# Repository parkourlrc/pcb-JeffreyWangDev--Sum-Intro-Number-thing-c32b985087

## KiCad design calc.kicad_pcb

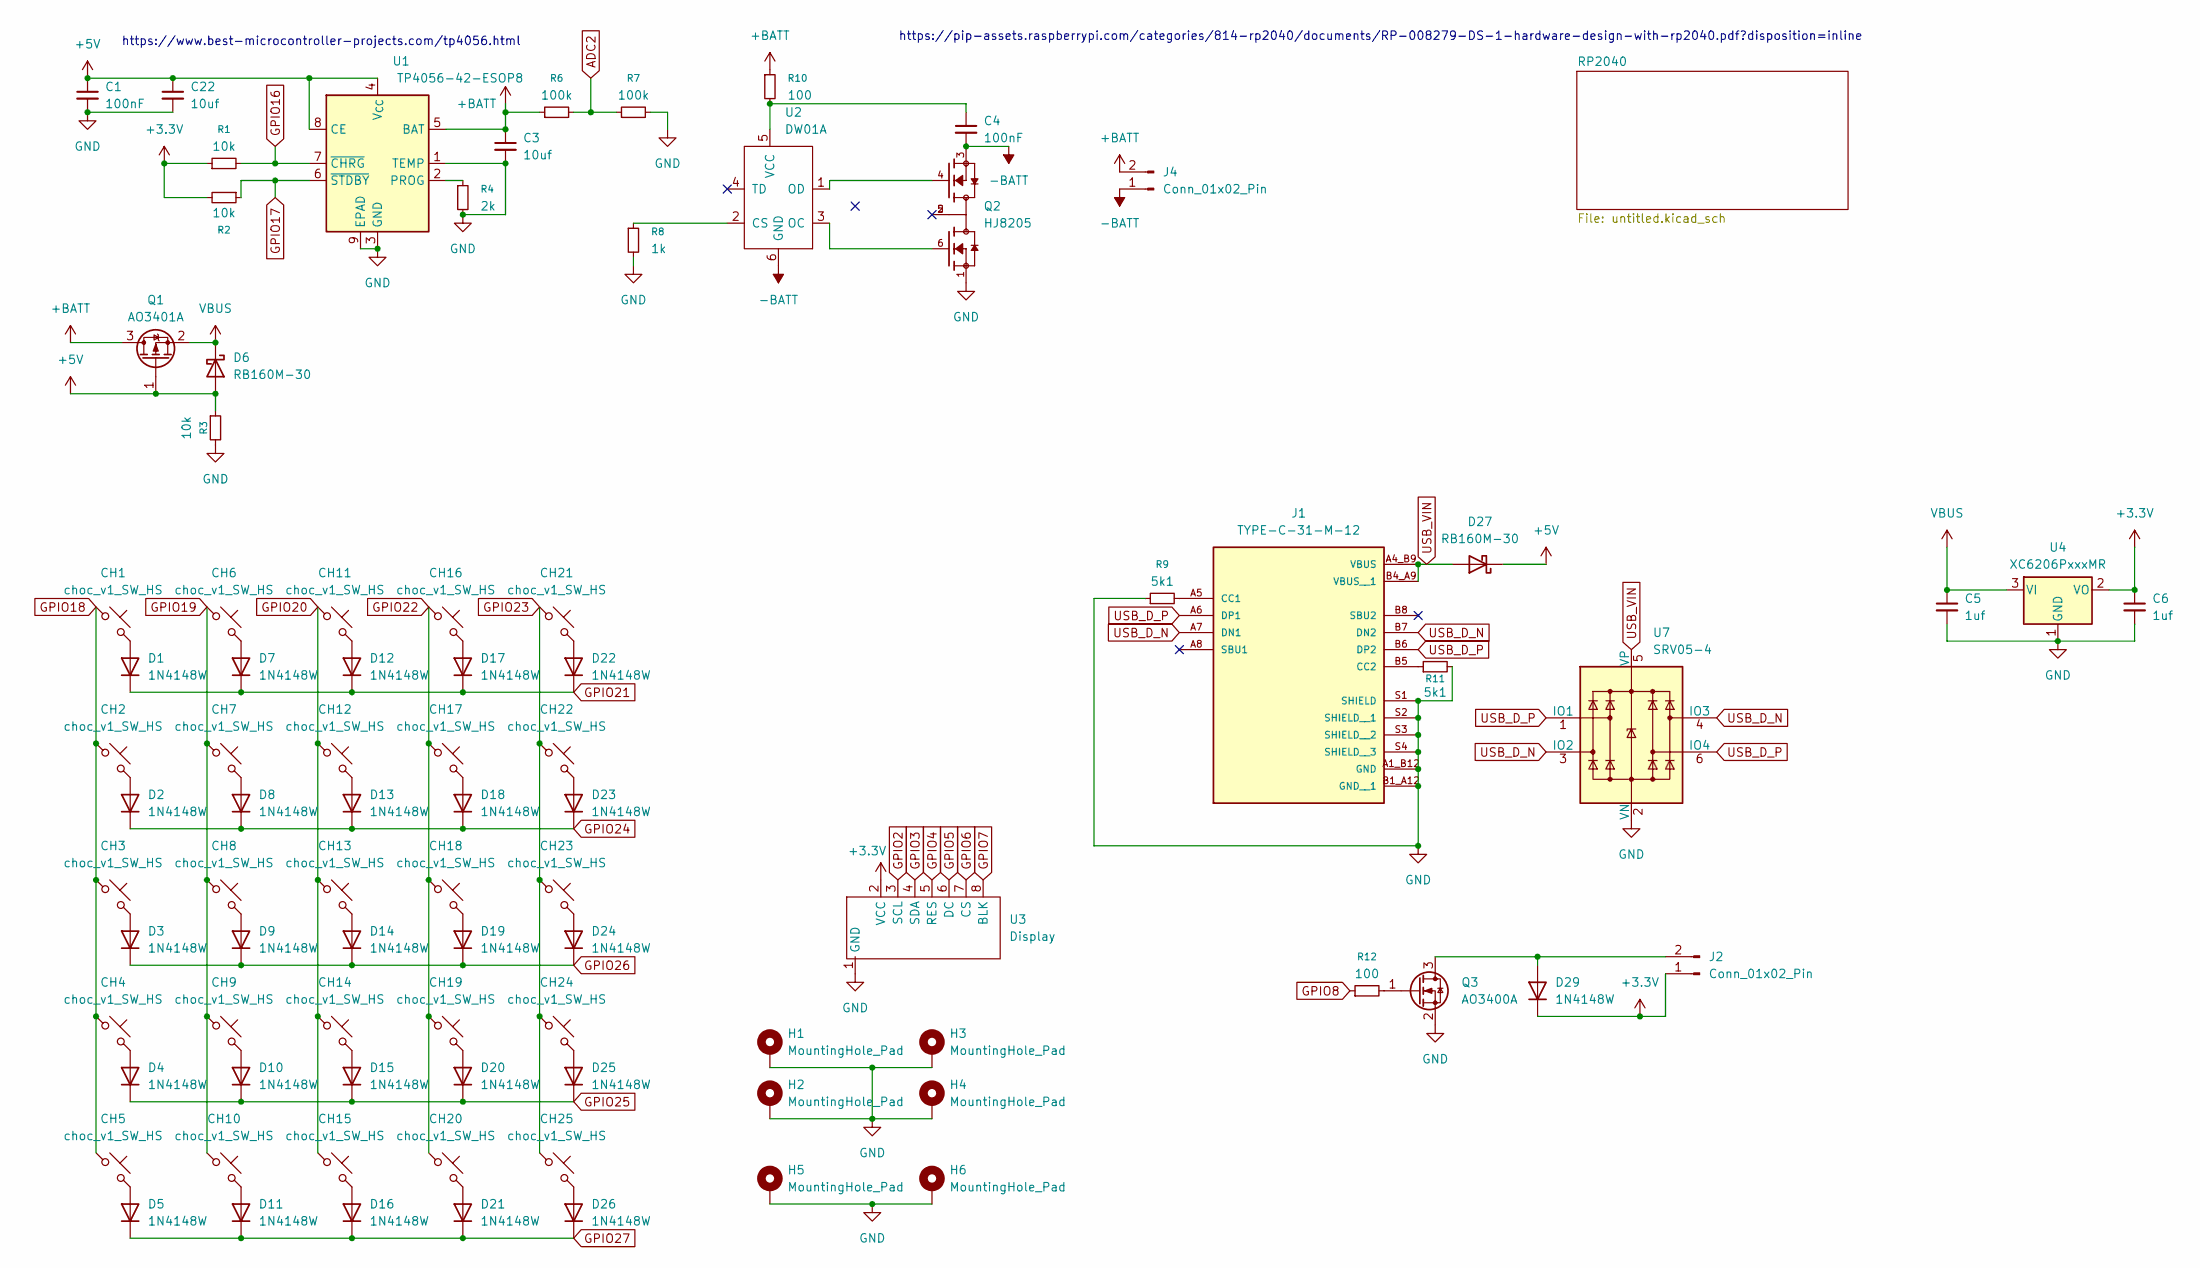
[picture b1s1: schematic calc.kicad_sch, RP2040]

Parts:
C1, C4: 100nF; C_0402_1005Metric; lcsc C1525
C3, C22: 10uf; C_0603_1608Metric; lcsc C96446
C5, C6: 1uf; C_0805_2012Metric_Pad1.18x1.45mm_HandSolder; lcsc C28323
CH1, CH2, CH3, CH4, CH5, CH6, CH7, CH8, CH9, CH10, CH11, CH12, CH13, CH14, CH15, CH16, CH17, CH18, CH19, CH20, CH21, CH22, CH23, CH24, CH25: choc_v1_SW_HS; SW_choc_v1_HS_CPG135001S30_1u
D1, D2, D3, D4, D5, D7, D8, D9, D10, D11, D12, D13, D14, D15, D16, D17, D18, D19, D20, D21, D22, D23, D24, D25, D26, D29: 1N4148W; D_SOD-123; lcsc C81598
D6, D27: RB160M-30; D_SOD-123; LCSC C7502715
H1, H2, H3, H4, H5, H6: MountingHole_Pad; MountingHole_3.2mm_M3_ISO14580_Pad_TopBottom
J1: TYPE-C-31-M-12; HRO_TYPE-C-31-M-12; PARTREV 2020.12.08; LCSC C165948
J2, J4: Conn_01x02_Pin; PinHeader_1x02_P2.00mm_Vertical
Q1: AO3401A; SOT-23; LCSC C15127
Q2: HJ8205; SOT-23-6; LCSC C20069150
Q3: AO3400A; SOT-23; lcsc C20917
R1, R2, R3: 10k; R_0805_2012Metric_Pad1.20x1.40mm_HandSolder; lcsc C17414
R4: 2k; R_0402_1005Metric; lcsc C4109
R6, R7: 100k; R_0603_1608Metric; lcsc C25803
R8: 1k; R_0402_1005Metric; lcsc C11702
R9, R11: 5k1; R_0402_1005Metric; lcsc C25905
R10, R12: 100; R_0805_2012Metric_Pad1.20x1.40mm_HandSolder; lcsc C17408
U1: TP4056-42-ESOP8; SOIC-8-1EP_3.9x4.9mm_P1.27mm_EP2.41x3.3mm_ThermalVias; LCSC C16581
U2: DW01A; SOT-23-6; LCSC C351410
U3: Display; 2.25_ TFT
U4: XC6206PxxxMR; SOT-23-3; LCSC C5446
U7: SRV05-4; SOT-23-6; lcsc C85364

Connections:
+3.3V: C6.1, D29.1 (K), J2.1, R1.1, R2.2, U3.2 (VCC), U4.2 (VO); also elsewhere on the board
+5V: C1.1, C22.1, D6.2 (A), D27.1 (K), Q1.1 (G), R3.1, U1.4 (V_{CC}), U1.8 (CE)
+BATT: C3.1, J4.2, Q1.3 (D), R6.1, R10.1, U1.5 (BAT)
-BATT: C4.2, J4.1, Q2.3, U2.6 (GND)
ADC2: R6.2, R7.1; also elsewhere on the board
GND: C1.2, C3.2, C5.2, C6.2, C22.2, H1.1 (1_1), H2.1 (1_1), H3.1 (1_1), H4.1 (1_1), H5.1 (1_1), H6.1 (1_1), J1.A1_B12 (GND), J1.B1_A12 (GND__1), J1.S1 (SHIELD), J1.S2 (SHIELD__1), J1.S3 (SHIELD__2), J1.S4 (SHIELD__3), Q2.1, Q3.2 (S), R3.2, R4.2, R7.2, R8.2, R9.1, R11.2, U1.1 (TEMP), U1.3 (GND), U1.9 (EPAD), U3.1 (GND), U4.1 (GND), U7.2 (VN); also elsewhere on the board
GPIO2: U3.3 (SCL); also elsewhere on the board
GPIO3: U3.4 (SDA); also elsewhere on the board
GPIO4: U3.5 (RES); also elsewhere on the board
GPIO5: U3.6 (DC); also elsewhere on the board
GPIO6: U3.7 (CS); also elsewhere on the board
GPIO7: U3.8 (BLK); also elsewhere on the board
GPIO8: R12.1; also elsewhere on the board
GPIO16: R1.2, U1.7 (~CHRG); also elsewhere on the board
GPIO17: R2.1, U1.6 (~STDBY); also elsewhere on the board
GPIO18: CH1.1, CH2.1, CH3.1, CH4.1, CH5.1; also elsewhere on the board
GPIO19: CH6.1, CH7.1, CH8.1, CH9.1, CH10.1; also elsewhere on the board
GPIO20: CH11.1, CH12.1, CH13.1, CH14.1, CH15.1; also elsewhere on the board
GPIO21: D1.1 (K), D7.1 (K), D12.1 (K), D17.1 (K), D22.1 (K); also elsewhere on the board
GPIO22: CH16.1, CH17.1, CH18.1, CH19.1, CH20.1; also elsewhere on the board
GPIO23: CH21.1, CH22.1, CH23.1, CH24.1, CH25.1; also elsewhere on the board
GPIO24: D2.1 (K), D8.1 (K), D13.1 (K), D18.1 (K), D23.1 (K); also elsewhere on the board
GPIO25: D4.1 (K), D10.1 (K), D15.1 (K), D20.1 (K), D25.1 (K); also elsewhere on the board
GPIO26: D3.1 (K), D9.1 (K), D14.1 (K), D19.1 (K), D24.1 (K); also elsewhere on the board
GPIO27: D5.1 (K), D11.1 (K), D16.1 (K), D21.1 (K), D26.1 (K); also elsewhere on the board
unnamed: CH1.2, D1.2 (A)
unnamed: CH2.2, D2.2 (A)
unnamed: CH3.2, D3.2 (A)
unnamed: CH4.2, D4.2 (A)
unnamed: CH5.2, D5.2 (A)
unnamed: CH6.2, D7.2 (A)
unnamed: CH7.2, D8.2 (A)
unnamed: CH8.2, D9.2 (A)
unnamed: CH9.2, D10.2 (A)
unnamed: CH10.2, D11.2 (A)
unnamed: CH11.2, D12.2 (A)
unnamed: CH12.2, D13.2 (A)
unnamed: CH13.2, D14.2 (A)
unnamed: CH14.2, D15.2 (A)
unnamed: CH15.2, D16.2 (A)
unnamed: CH16.2, D17.2 (A)
unnamed: CH17.2, D18.2 (A)
unnamed: CH18.2, D19.2 (A)
unnamed: CH19.2, D20.2 (A)
unnamed: CH20.2, D21.2 (A)
unnamed: CH21.2, D22.2 (A)
unnamed: CH22.2, D23.2 (A)
unnamed: CH23.2, D24.2 (A)
unnamed: CH24.2, D25.2 (A)
unnamed: CH25.2, D26.2 (A)
unnamed: D29.2 (A), J2.2, Q3.3 (D)
unnamed: J1.A5 (CC1), R9.2
unnamed: J1.B5 (CC2), R11.1
unnamed: Q3.1 (G), R12.2
unnamed: R4.1, U1.2 (PROG)
unnamed: R8.1, U2.2 (CS)
unnamed: Q2.6, U2.3 (OC)
unnamed: Q2.4, U2.1 (OD)
unnamed: C4.1, R10.2, U2.5 (VCC)
USB_D_N: J1.A7 (DN1), J1.B7 (DN2), U7.3 (IO2), U7.4 (IO3); also elsewhere on the board
USB_D_P: J1.A6 (DP1), J1.B6 (DP2), U7.1 (IO1), U7.6 (IO4); also elsewhere on the board
USB_VIN: D27.2 (A), J1.A4_B9 (VBUS), J1.B4_A9 (VBUS__1), U7.5 (VP)
VBUS: C5.1, D6.1 (K), Q1.2 (S), U4.3 (VI)

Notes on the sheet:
https://www.best-microcontroller-projects.com/tp4056.html
https://pip-assets.raspberrypi.com/categories/814-rp2040/documents/RP-008279-DS-1-hardware-design-with-rp2040.pdf?disposition=inline

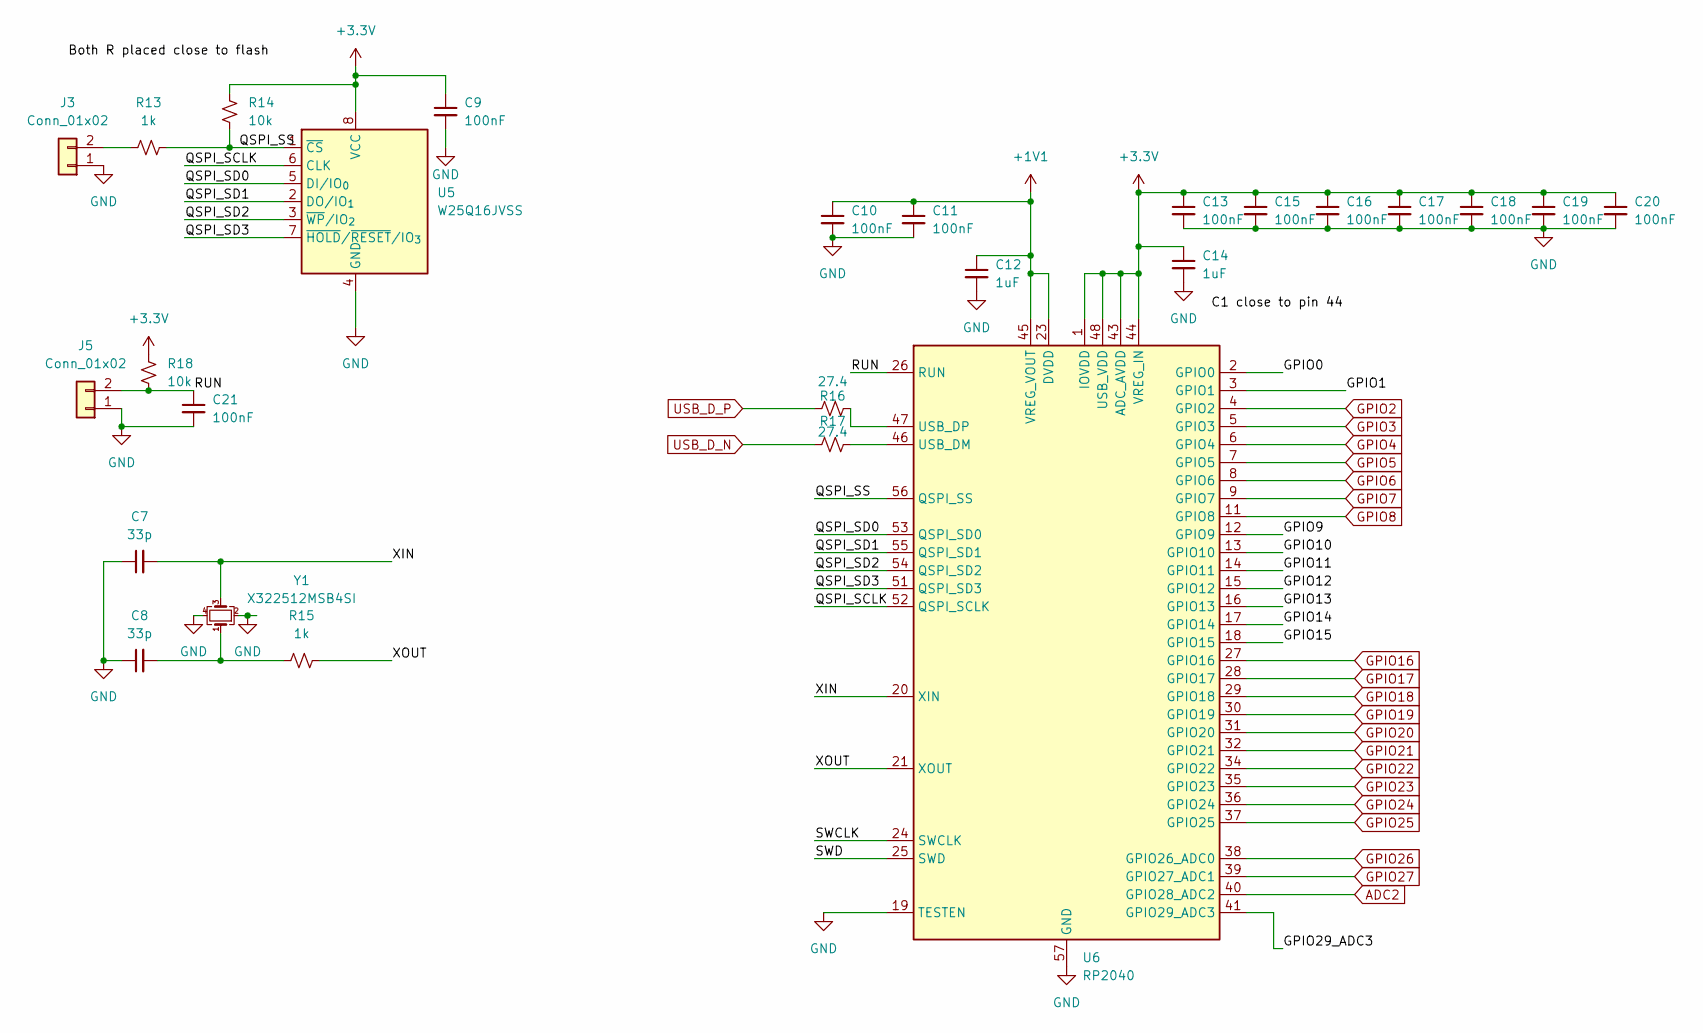
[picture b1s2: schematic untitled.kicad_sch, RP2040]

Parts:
C7, C8: 33p; C_0402_1005Metric; lcsc C1562
C9, C10, C11, C13, C15, C16, C17, C18, C19, C20, C21: 100nF; C_0402_1005Metric; lcsc C1525
C12, C14: 1uF; C_0603_1608Metric; lcsc C14663
J3, J5: Conn_01x02; PinHeader_1x02_P2.00mm_Vertical
R13, R15: 1k; R_0402_1005Metric; lcsc C11702
R14, R18: 10k; R_0805_2012Metric_Pad1.20x1.40mm_HandSolder; lcsc C17414
R16, R17: 27.4; R_0805_2012Metric_Pad1.20x1.40mm_HandSolder; lcsc C17588
U5: W25Q16JVSS; SOIC-8_5.3x5.3mm_P1.27mm; lcsc C131025
U6: RP2040; QFN-56-1EP_7x7mm_P0.4mm_EP3.2x3.2mm; lcsc C2040
Y1: X322512MSB4SI; Crystal_SMD_Abracon_ABM8G-4Pin_3.2x2.5mm; lcsc C9002

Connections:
+1V1: C10.1, C11.1, C12.1, U6.23 (DVDD), U6.45 (VREG_VOUT), U6.50 (DVDD)
+3.3V: C9.1, C13.1, C14.1, C15.1, C16.1, C17.1, C18.1, C19.1, C20.1, R14.1, R18.1, U5.8 (VCC), U6.1 (IOVDD), U6.10 (IOVDD), U6.22 (IOVDD), U6.33 (IOVDD), U6.42 (IOVDD), U6.43 (ADC_AVDD), U6.44 (VREG_IN), U6.48 (USB_VDD), U6.49 (IOVDD); also elsewhere on the board
/RP2040/GPIO0: U6.2 (GPIO0)
/RP2040/GPIO1: U6.3 (GPIO1)
/RP2040/GPIO9: U6.12 (GPIO9)
/RP2040/GPIO10: U6.13 (GPIO10)
/RP2040/GPIO11: U6.14 (GPIO11)
/RP2040/GPIO12: U6.15 (GPIO12)
/RP2040/GPIO13: U6.16 (GPIO13)
/RP2040/GPIO14: U6.17 (GPIO14)
/RP2040/GPIO15: U6.18 (GPIO15)
/RP2040/GPIO29_ADC3: U6.41 (GPIO29_ADC3)
/RP2040/QSPI_SCLK: U5.6 (CLK), U6.52 (QSPI_SCLK)
/RP2040/QSPI_SD0: U5.5 (DI/IO_{0}), U6.53 (QSPI_SD0)
/RP2040/QSPI_SD1: U5.2 (DO/IO_{1}), U6.55 (QSPI_SD1)
/RP2040/QSPI_SD2: U5.3 (~WP/IO_{2}), U6.54 (QSPI_SD2)
/RP2040/QSPI_SD3: U5.7 (~HOLD/~RESET/IO_{3}), U6.51 (QSPI_SD3)
/RP2040/QSPI_SS: R13.2, R14.2, U5.1 (~CS), U6.56 (QSPI_SS)
/RP2040/RUN: C21.1, J5.2, R18.2, U6.26 (RUN)
/RP2040/SWCLK: U6.24 (SWCLK)
/RP2040/SWD: U6.25 (SWD)
/RP2040/XIN: C7.2, U6.20 (XIN), Y1.3
/RP2040/XOUT: R15.2, U6.21 (XOUT)
ADC2: U6.40 (GPIO28_ADC2); also elsewhere on the board
GND: C7.1, C8.1, C9.2, C10.2, C11.2, C12.2, C13.2, C14.2, C15.2, C16.2, C17.2, C18.2, C19.2, C20.2, C21.2, J3.1, J5.1, U5.4 (GND), U6.19 (TESTEN), U6.57 (GND), Y1.2, Y1.4; also elsewhere on the board
GPIO2: U6.4 (GPIO2); also elsewhere on the board
GPIO3: U6.5 (GPIO3); also elsewhere on the board
GPIO4: U6.6 (GPIO4); also elsewhere on the board
GPIO5: U6.7 (GPIO5); also elsewhere on the board
GPIO6: U6.8 (GPIO6); also elsewhere on the board
GPIO7: U6.9 (GPIO7); also elsewhere on the board
GPIO8: U6.11 (GPIO8); also elsewhere on the board
GPIO16: U6.27 (GPIO16); also elsewhere on the board
GPIO17: U6.28 (GPIO17); also elsewhere on the board
GPIO18: U6.29 (GPIO18); also elsewhere on the board
GPIO19: U6.30 (GPIO19); also elsewhere on the board
GPIO20: U6.31 (GPIO20); also elsewhere on the board
GPIO21: U6.32 (GPIO21); also elsewhere on the board
GPIO22: U6.34 (GPIO22); also elsewhere on the board
GPIO23: U6.35 (GPIO23); also elsewhere on the board
GPIO24: U6.36 (GPIO24); also elsewhere on the board
GPIO25: U6.37 (GPIO25); also elsewhere on the board
GPIO26: U6.38 (GPIO26_ADC0); also elsewhere on the board
GPIO27: U6.39 (GPIO27_ADC1); also elsewhere on the board
unnamed: C8.2, R15.1, Y1.1
unnamed: J3.2, R13.1
unnamed: R17.2, U6.46 (USB_DM)
unnamed: R16.2, U6.47 (USB_DP)
USB_D_N: R17.1; also elsewhere on the board
USB_D_P: R16.1; also elsewhere on the board

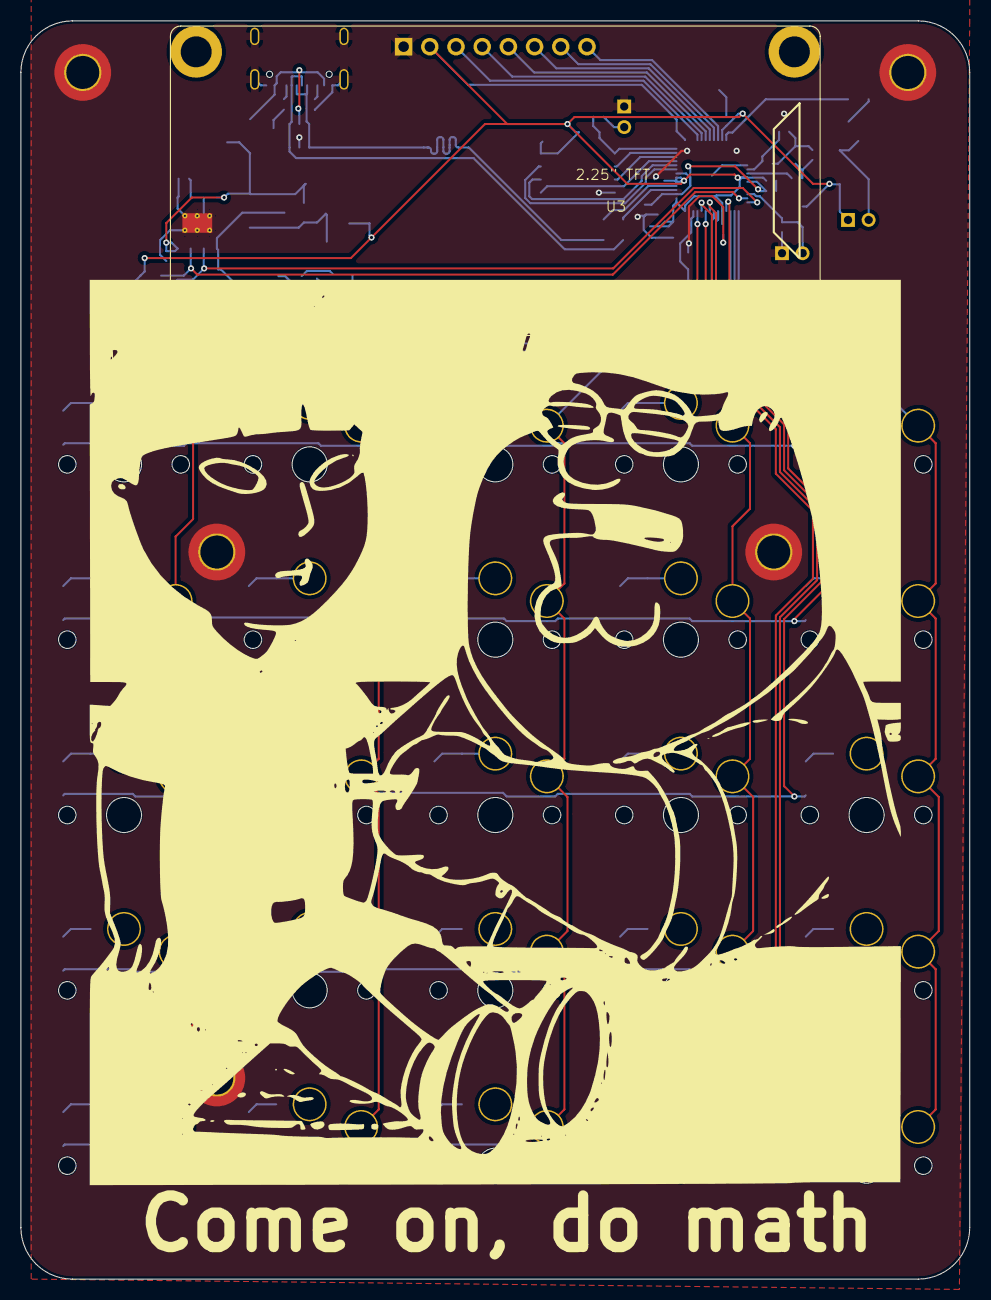
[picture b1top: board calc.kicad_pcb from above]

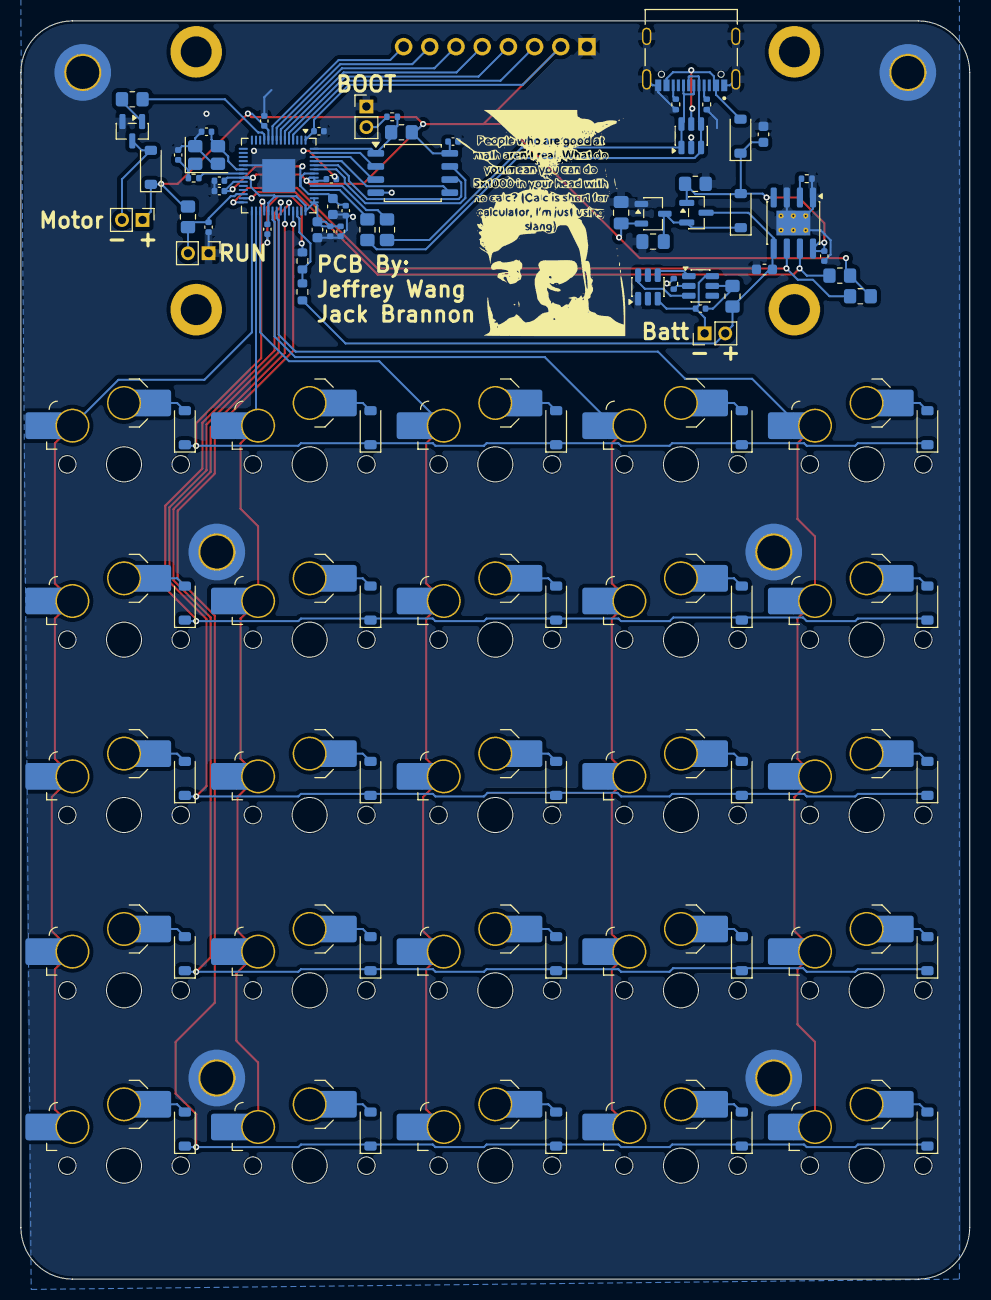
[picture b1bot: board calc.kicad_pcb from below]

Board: 2 copper layers, 92.0 x 122.0 mm, 113 parts (106 on the bottom side), 77 nets.

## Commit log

2026-03-31 PWR
    Added load sharing
2026-04-08 make CALc
2026-04-08 Update Schematic
2026-04-08 Add traces
    3 Components left to place
2026-04-08 lcsc data
2026-04-08 update traces and footprints
2026-04-08 mote trace stuff
2026-04-08 final hope
2026-04-09 update more
2026-04-09 updated run
2026-04-09 added silkscreen
2026-04-09 update silk
2026-04-10 final
